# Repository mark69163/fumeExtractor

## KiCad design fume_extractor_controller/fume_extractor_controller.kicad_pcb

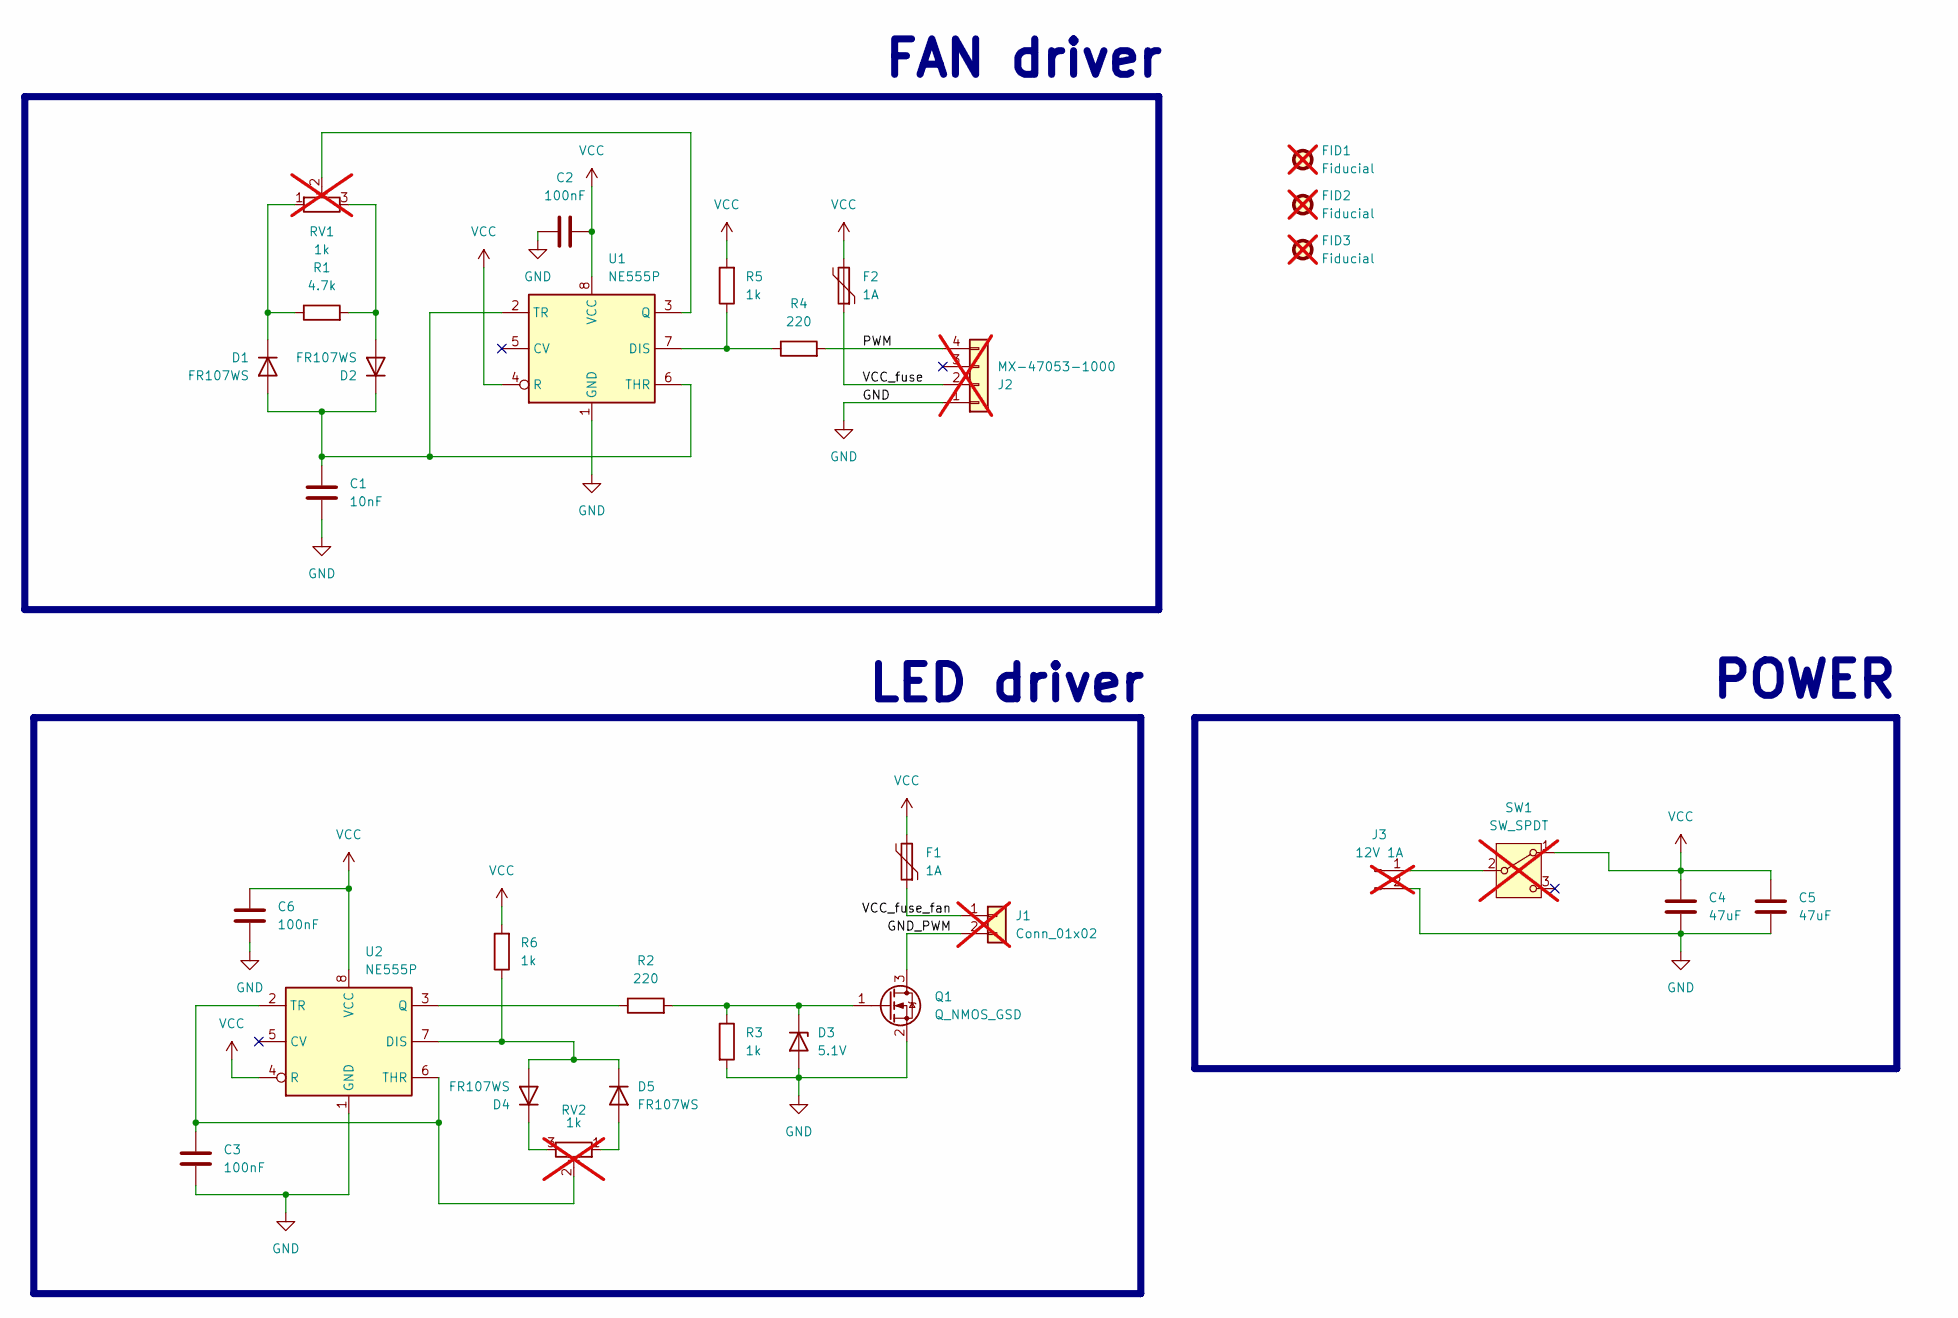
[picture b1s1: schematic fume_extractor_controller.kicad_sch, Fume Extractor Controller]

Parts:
C1: 10nF; C_0603_1608Metric; MPN C100042
C2, C3, C6: 100nF; C_0603_1608Metric; MPN C1591
C4, C5: 47uF; C_1210_3225Metric; MPN C90142
D1, D2, D4, D5: FR107WS; D_SOD-323_HandSoldering; MPN C3013756
D3: 5.1V; D_SOD-323_HandSoldering; MPN C2891762
F1, F2: 1A; Fuse_0603_1608Metric; MPN C151139
FID1, FID2, FID3: Fiducial; Fiducial_0.75mm_Mask1.5mm; not fitted
J1: Conn_01x02; Wire_pad_1x2_P1.27; not fitted
J2: MX-47053-1000; FanPinHeader_1x04_P2.54mm_Vertical; MPN MX-47053-1000; not fitted
J3: 12V 1A; Wire_Pad_1x2_2.54P; not fitted
Q1: Q_NMOS_GSD; SOT-23; MPN C4748722
R1: 4.7k; R_0603_1608Metric; MPN C23162
R2, R4: 220; R_0603_1608Metric; MPN C22962
R3, R5, R6: 1k; R_0603_1608Metric; MPN C22548
RV1, RV2: 1k; Potentiometer_Piher_PT-6-H_Horizontal; MPN PT6LH-1K; not fitted
SW1: SW_SPDT; SW_Slide_SPDT_Angled_CK_OS102011MA1Q; MPN OS102011MA1QN1; not fitted
U1, U2: NE555P; TSSOP-8_4.4x3mm_P0.65mm; MPN C105643

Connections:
/GND_PWM: J1.2, Q1.3 (D)
/PWM: J2.4, R4.2
/VCC_fuse: F2.1, J2.2
/VCC_fuse_fan: F1.1, J1.1
GND: C1.2, C2.1, C3.1, C4.2, C5.2, C6.1, D3.2 (A), J2.1, J3.2, Q1.2 (S), R3.2, U1.1 (GND), U2.1 (GND)
unnamed: C1.1, D1.2 (A), D2.1 (K), U1.2 (TR), U1.6 (THR)
unnamed: D1.1 (K), R1.1, RV1.1
unnamed: D2.2 (A), R1.2, RV1.3
unnamed: D3.1 (K), Q1.1 (G), R2.2, R3.1
unnamed: D4.2 (A), D5.1 (K), R6.1, U2.7 (DIS)
unnamed: D4.1 (K), RV2.3
unnamed: D5.2 (A), RV2.1
unnamed: J3.1, SW1.2 (B)
unnamed: R4.1, R5.1, U1.7 (DIS)
unnamed: RV1.2, U1.3 (Q)
unnamed: R2.1, U2.3 (Q)
unnamed: C3.2, RV2.2, U2.2 (TR), U2.6 (THR)
VCC: C2.2, C4.1, C5.1, C6.2, F1.2, F2.2, R5.2, R6.2, SW1.1 (A), U1.4 (R), U1.8 (VCC), U2.4 (R), U2.8 (VCC)

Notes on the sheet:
POWER
FAN driver
LED driver

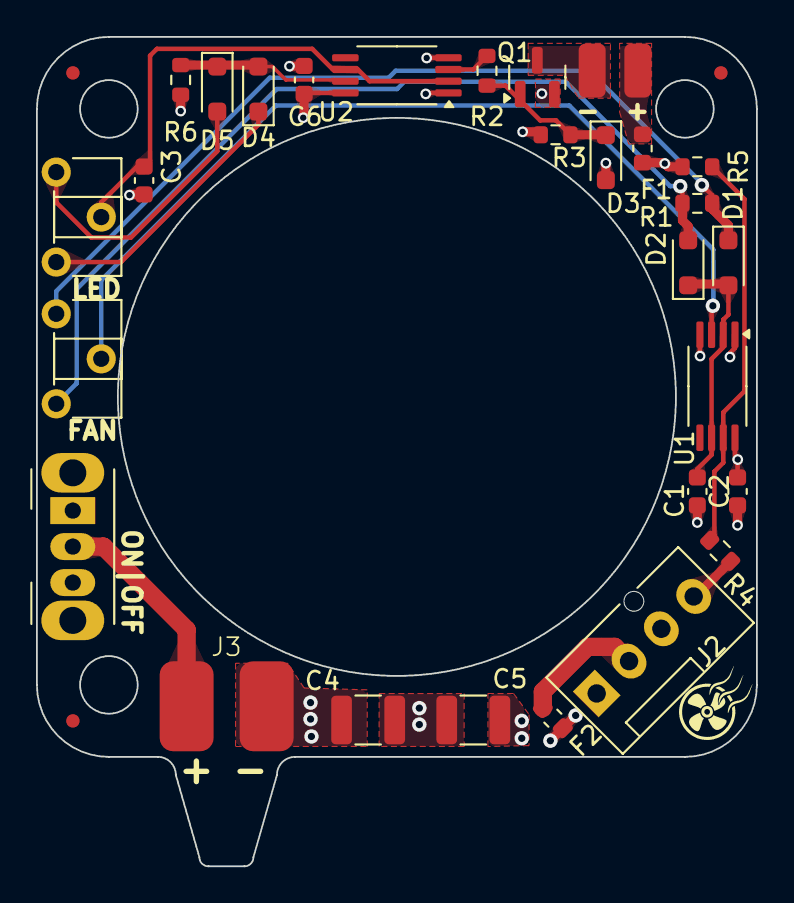
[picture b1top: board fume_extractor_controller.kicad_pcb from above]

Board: 4 copper layers, 40.0 x 46.1 mm, 31 parts (0 on the bottom side), 18 nets.

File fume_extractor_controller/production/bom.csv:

Designator,Footprint,Quantity,Value,LCSC Part #
C1,0603,1,10nF,C100042
"C2, C3, C6",0603,3,100nF,C1591
"C4, C5",1210,2,47uF,C90142
"D1, D2, D4, D5",D_SOD-323_HandSoldering,4,FR107WS,C3013756
D3,D_SOD-323_HandSoldering,1,5.1V,C2891762
"F1, F2",0603,2,1A,C151139
Q1,SOT-23,1,Q_NMOS_GSD,C4748722
R1,0603,1,4.7k,C23162
"R2, R4",0603,2,220,C22962
"R3, R5, R6",0603,3,1k,C22548
"U1, U2",TSSOP-8_4.4x3mm_P0.65mm,2,NE555P,C105643

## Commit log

2024-05-19 3d commit
2024-05-19 first backup
2024-05-20 Added part numbers and changed mosfet from gds to gsd.
2024-05-20 v1_20052024 added. Production docs generated.
2024-05-20 verion that i ordered.
2024-05-20 final version with html bom and changed component.
